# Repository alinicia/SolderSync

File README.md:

# SolderSync PCB Design
Modification of the T-962 reflow owen, ESP32 core with TFT LCD &amp; Custom Profiles

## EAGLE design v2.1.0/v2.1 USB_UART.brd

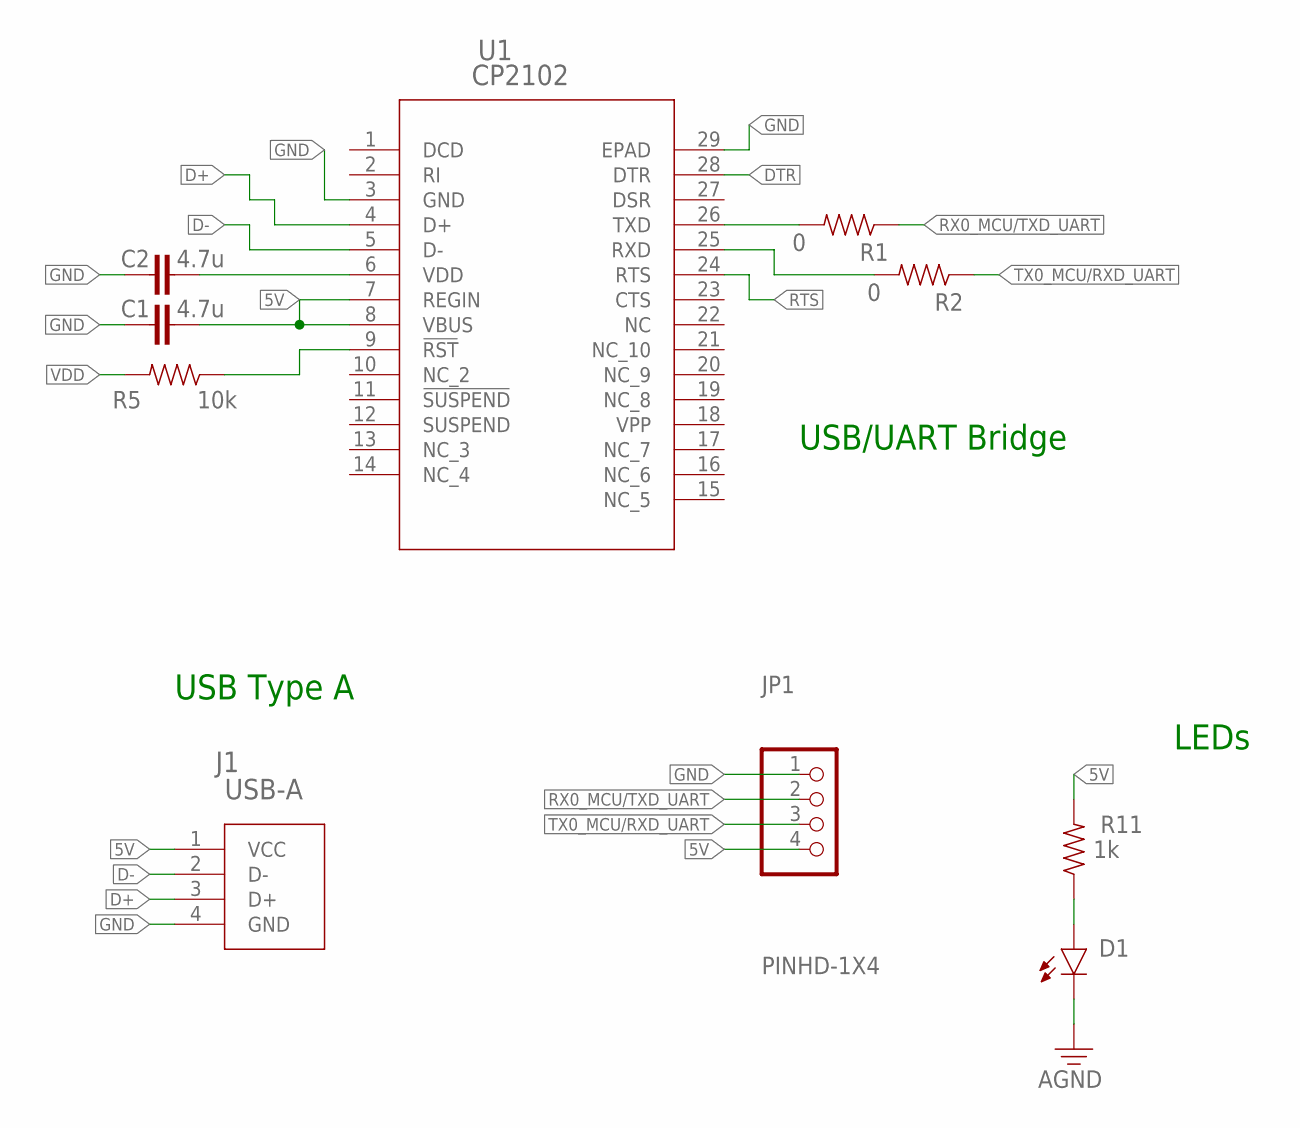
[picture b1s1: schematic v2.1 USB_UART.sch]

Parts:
C1, C2: 4.7u; CAPC2012X110
D1: LED; LEDC2012X110N_FLAT-B
J1: USB-A
JP1: PINHD-1X4; 1X04
R1, R2: 0; RESC2012X65
R5: 10k; RESC2012X65
R11: 1k; RESC2012X65
U1: CP2102; QFN28_5X5_SIL

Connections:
5V: C1.2, J1.1 (VCC), JP1.4, R11.2, U1.7 (REGIN), U1.8 (VBUS)
D+: J1.3 (D+), U1.4 (D+)
D-: J1.2 (D-), U1.5 (D-)
DTR: U1.28 (DTR)
GND: C1.1, C2.1, D1.C, J1.4 (GND), JP1.1, U1.3 (GND), U1.29 (EPAD)
unnamed: D1.A, R11.1
unnamed: R5.1, U1.9 (!RST)
RTS: U1.24 (RTS)
RX0_MCU/TXD_UART: JP1.2, R1.1
RXD: R2.2, U1.25 (RXD)
TX0_MCU/RXD_UART: JP1.3, R2.1
TXD: R1.2, U1.26 (TXD)
VDD: C2.2, R5.2, U1.6 (VDD)

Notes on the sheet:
USB/UART Bridge
USB Type A
LEDs

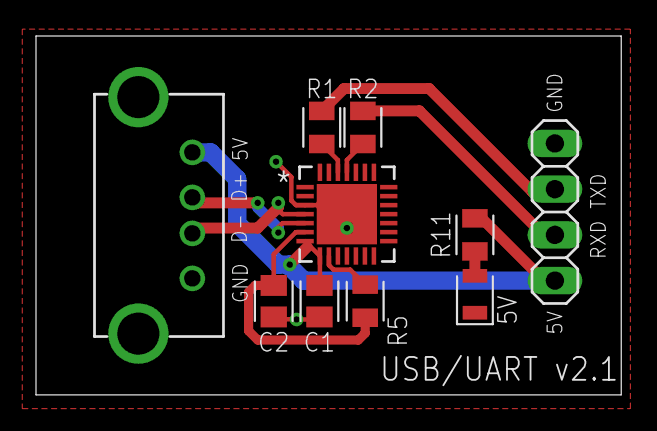
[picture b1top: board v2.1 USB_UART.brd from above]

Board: 2 copper layers, 32.5 x 19.9 mm, 10 parts (0 on the bottom side), 11 nets.

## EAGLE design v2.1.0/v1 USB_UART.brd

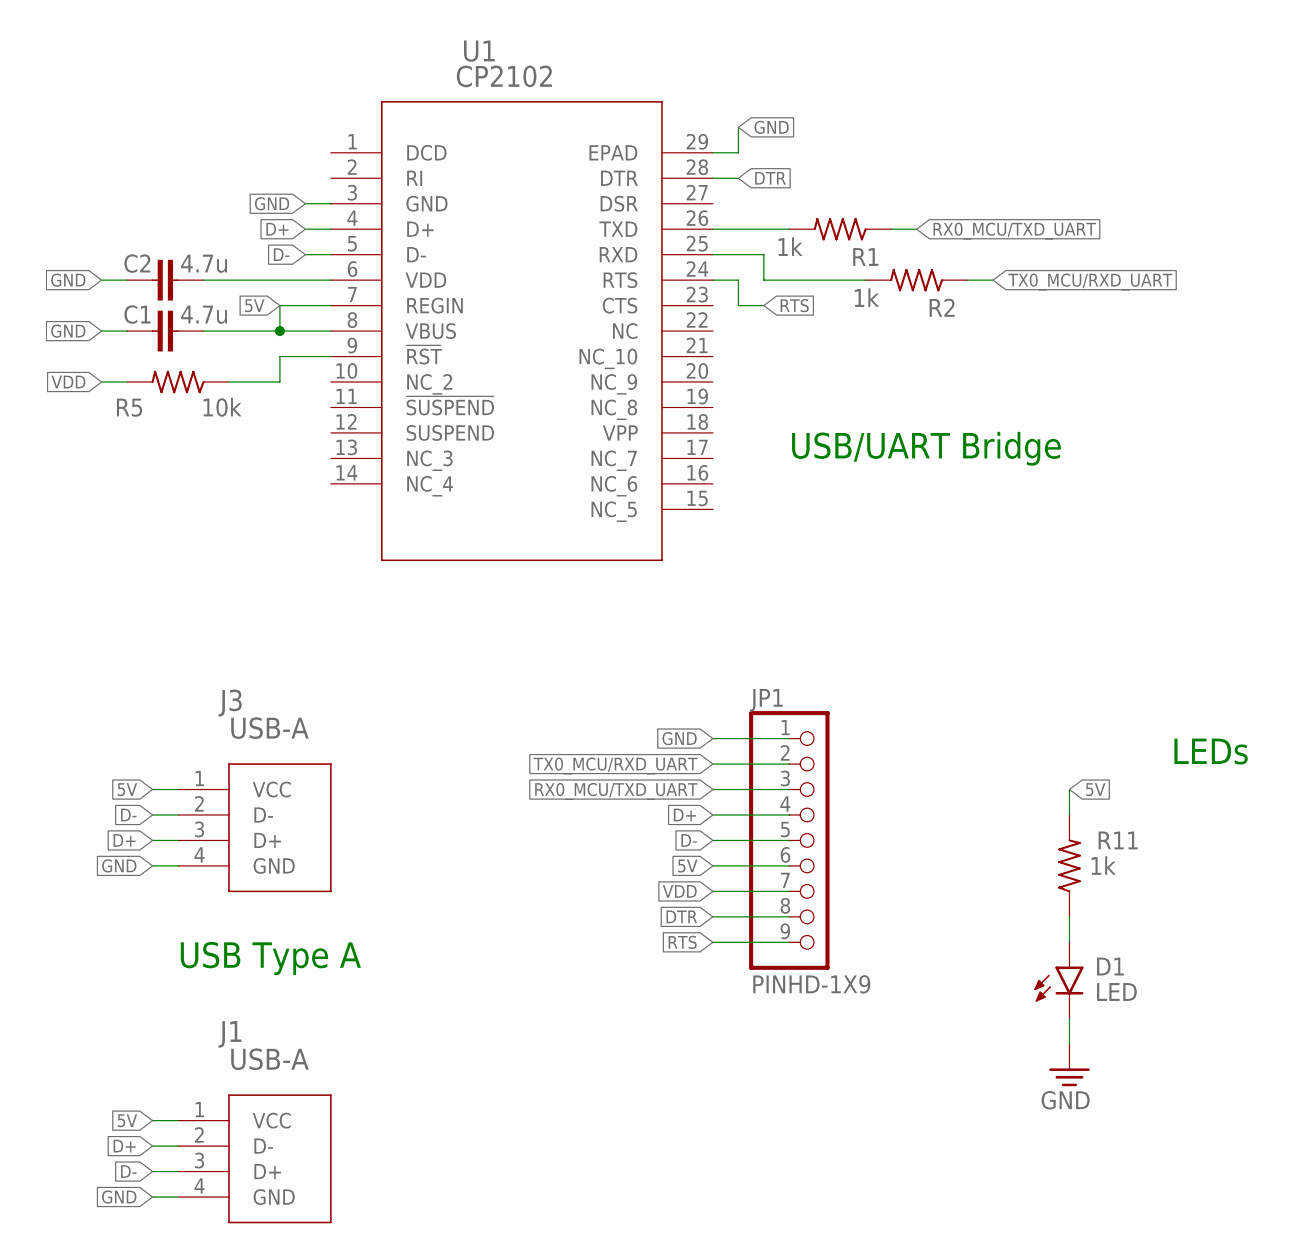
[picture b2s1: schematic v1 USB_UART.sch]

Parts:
C1, C2: 4.7u; CAPC2012X110
D1: LED; LEDC2012X110N_FLAT-B
J1, J3: USB-A
JP1: PINHD-1X9; 1X09
R1, R2, R11: 1k; RESC2012X65
R5: 10k; RESC2012X65
U1: CP2102; QFN28_5X5_SIL

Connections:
5V: C1.2, J1.1 (VCC), J3.1 (VCC), JP1.6, R11.2, U1.7 (REGIN), U1.8 (VBUS)
D+: J1.2 (D-), J3.3 (D+), JP1.4, U1.4 (D+)
D-: J1.3 (D+), J3.2 (D-), JP1.5, U1.5 (D-)
DTR: JP1.8, U1.28 (DTR)
GND: C1.1, C2.1, D1.C, J1.4 (GND), J3.4 (GND), JP1.1, U1.3 (GND), U1.29 (EPAD)
unnamed: D1.A, R11.1
unnamed: R5.1, U1.9 (!RST)
RTS: JP1.9, U1.24 (RTS)
RX0_MCU/TXD_UART: JP1.3, R1.1
RXD: R2.2, U1.25 (RXD)
TX0_MCU/RXD_UART: JP1.2, R2.1
TXD: R1.2, U1.26 (TXD)
VDD: C2.2, JP1.7, R5.2, U1.6 (VDD)

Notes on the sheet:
USB/UART Bridge
USB Type A
LEDs

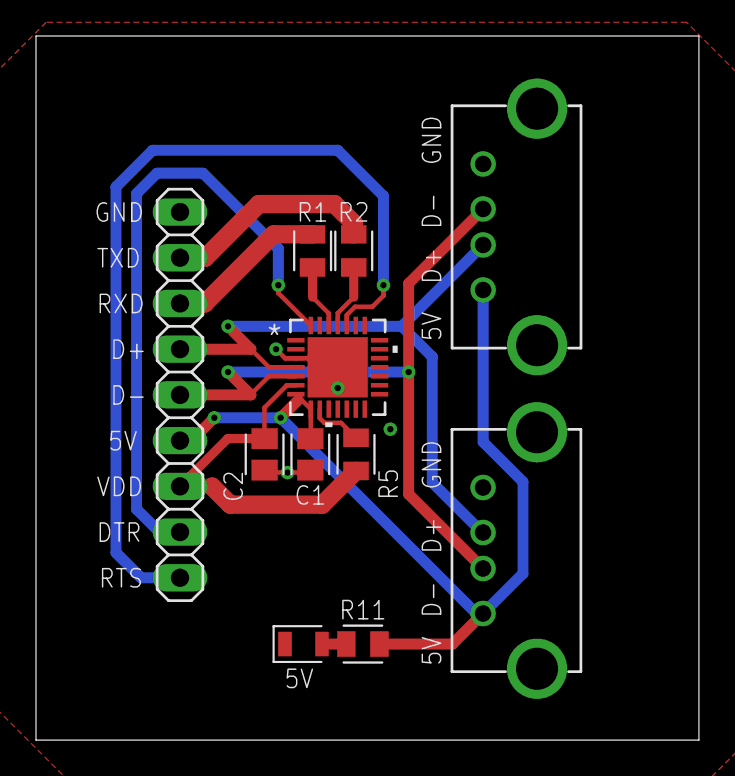
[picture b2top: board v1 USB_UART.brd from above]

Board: 2 copper layers, 36.8 x 39.1 mm, 11 parts (0 on the bottom side), 13 nets.

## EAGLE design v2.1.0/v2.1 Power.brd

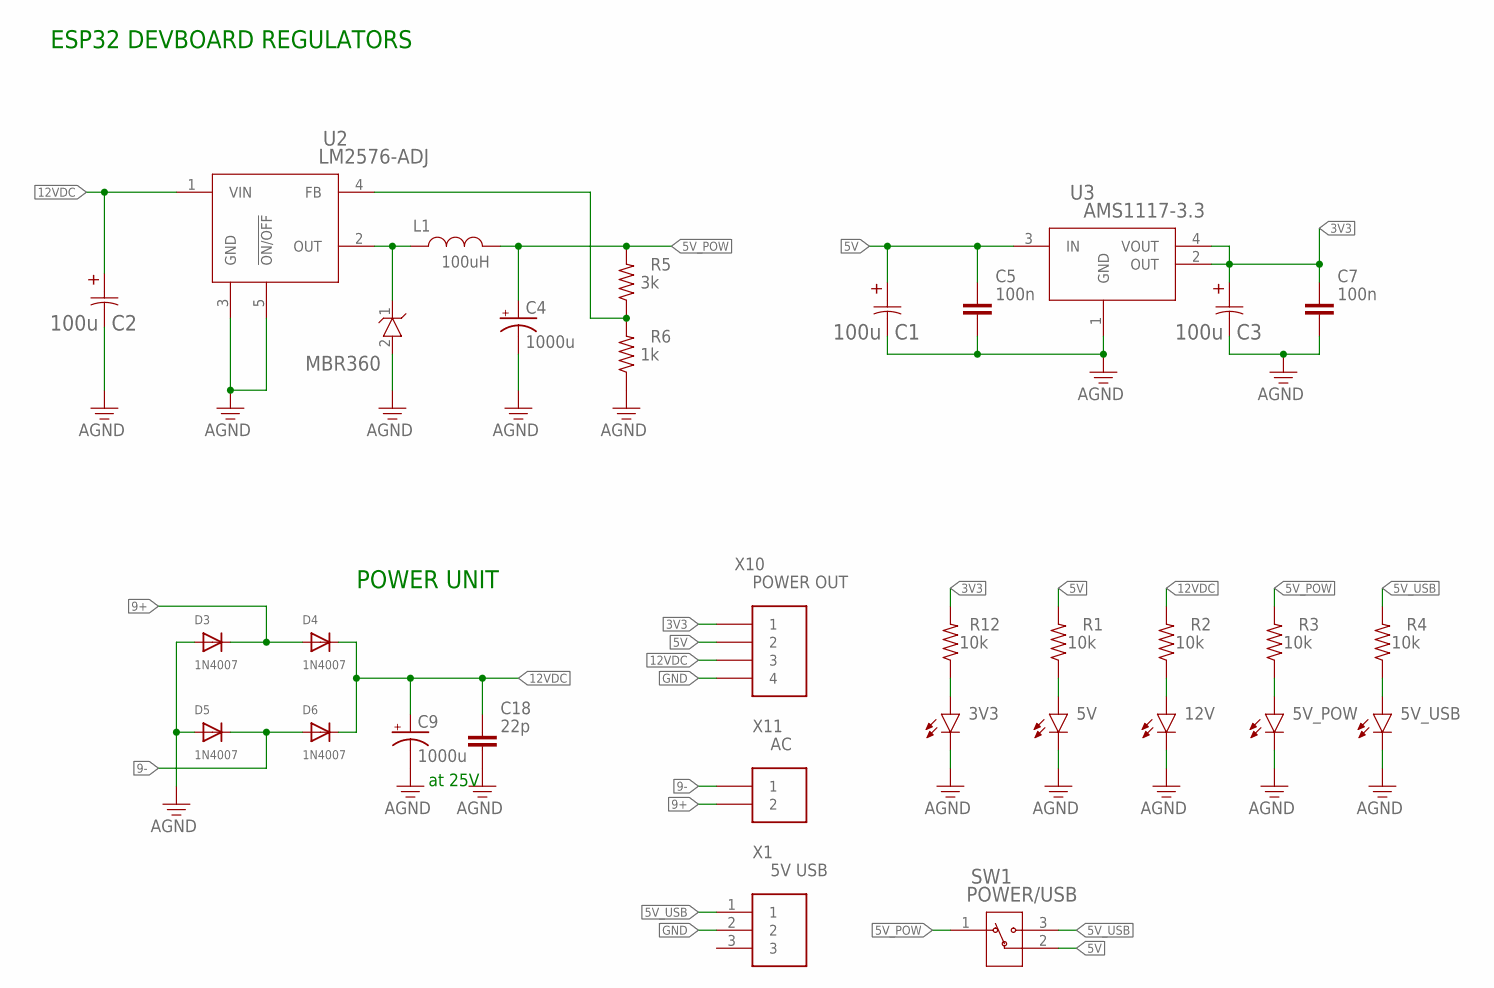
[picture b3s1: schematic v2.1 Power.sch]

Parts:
3V3, 5V, 5V_POW, 5V_USB, 12V: LED; LEDC2012X110N_FLAT-B
C1, C2, C3: 100u; 100UF_CAP
C4, C9: 1000u; CAP_10X20IN
C5, C7: 100n; CAPC2012X110
C18: 22p; CAPC2012X110
D3, D4, D5, D6: 1N4007; SOD-123FL
L1: 100uH; IND_MURATA_2200_MUR
MBR360: MBR360RLGDO-201AD_ONS; DO-201AD_ONS
R1, R2, R3, R4, R12: 10k; RESC2012X65
R5: 3k; RESC2012X65
R6: 1k; RESC2012X65
SW1: POWER/USB; SS-12D10G5_XKB
U2: LM2576-ADJ; T05A_TEX
U3: AMS1117-3.3; _ADS-L
X1: 5V USB; JST-XH-03-PACKAGE-LONG-PAD
X10: POWER OUT; JST-XH-04-PACKAGE-LONG-PAD
X11: AC; -LONG-PAD

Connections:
3V3: C3.1, C7.1, R12.2, U3.2 (OUT), U3.4 (VOUT), X10.1
5V: C1.1, C5.1, R1.2, SW1.2, U3.3 (IN), X10.2
5V_POW: C4.1 (+), L1.1, R3.2, R5.2, SW1.1
5V_USB: R4.2, SW1.3, X1.1
9+: D3.C, D4.A, X11.2
9-: D5.C, D6.A, X11.1
12VDC: C2.1, C9.1 (+), C18.1, D4.C, D6.C, R2.2, U2.1 (VIN), X10.3
FB: R5.1, R6.2, U2.4 (FB)
GND: 3V3.C, 5V.C, 5V_POW.C, 5V_USB.C, 12V.C, C1.2, C2.2, C3.2, C4.2 (-), C5.2, C7.2, C9.2 (-), C18.2, D3.A, D5.A, MBR360.2 (ANODE), R6.1, U2.3 (GND), U2.5 (!ON/OFF), U3.1 (GND), X1.2, X10.4
unnamed: 5V.A, R1.1
unnamed: L1.2, MBR360.1 (CATHODE), U2.2 (OUT)
unnamed: 12V.A, R2.1
unnamed: 5V_POW.A, R3.1
unnamed: 5V_USB.A, R4.1
unnamed: 3V3.A, R12.1

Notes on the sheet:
ESP32 DEVBOARD REGULATORS
POWER UNIT
at 25V

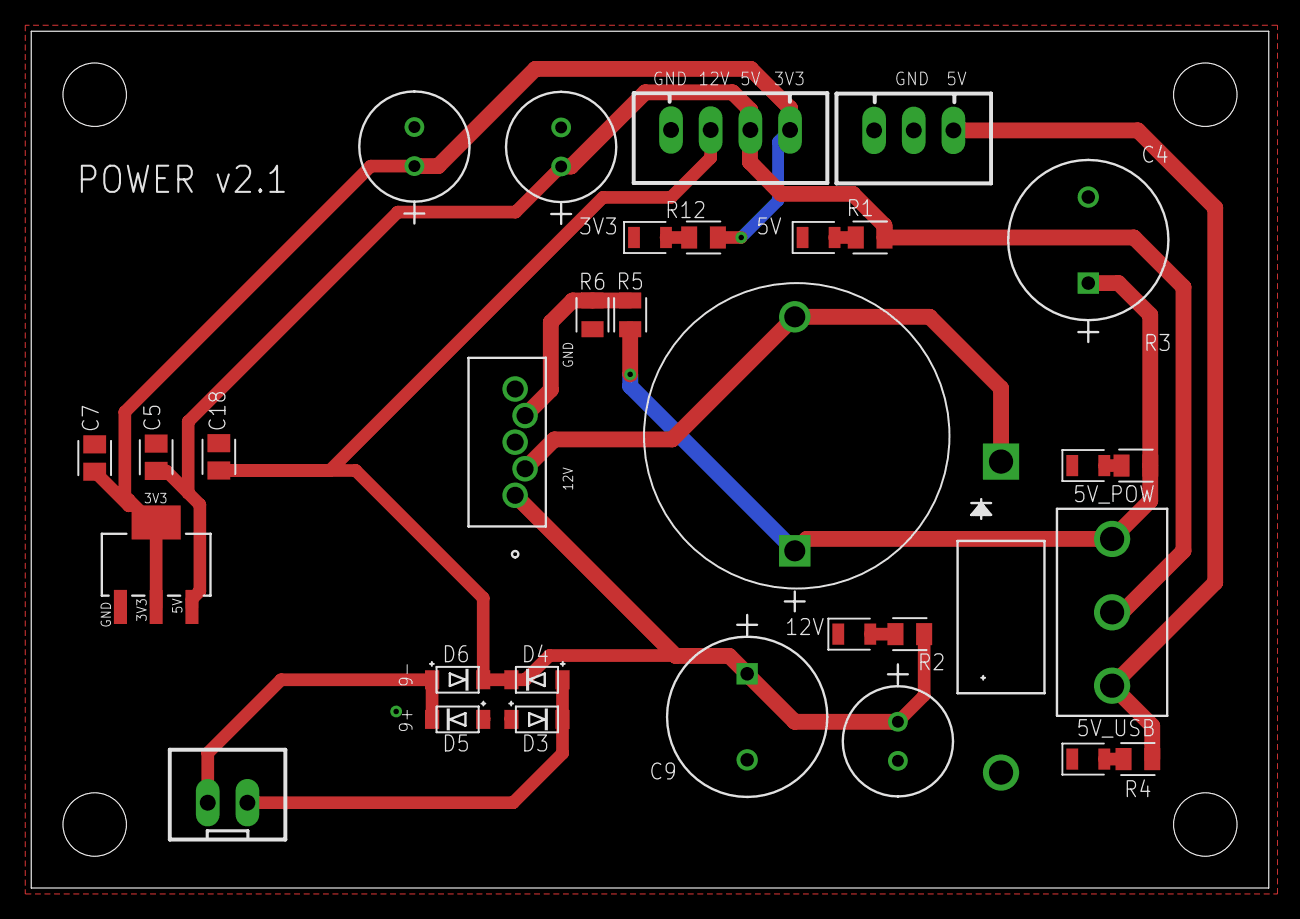
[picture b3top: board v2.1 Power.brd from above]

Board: 2 copper layers, 79.2 x 54.9 mm, 32 parts (0 on the bottom side), 15 nets.

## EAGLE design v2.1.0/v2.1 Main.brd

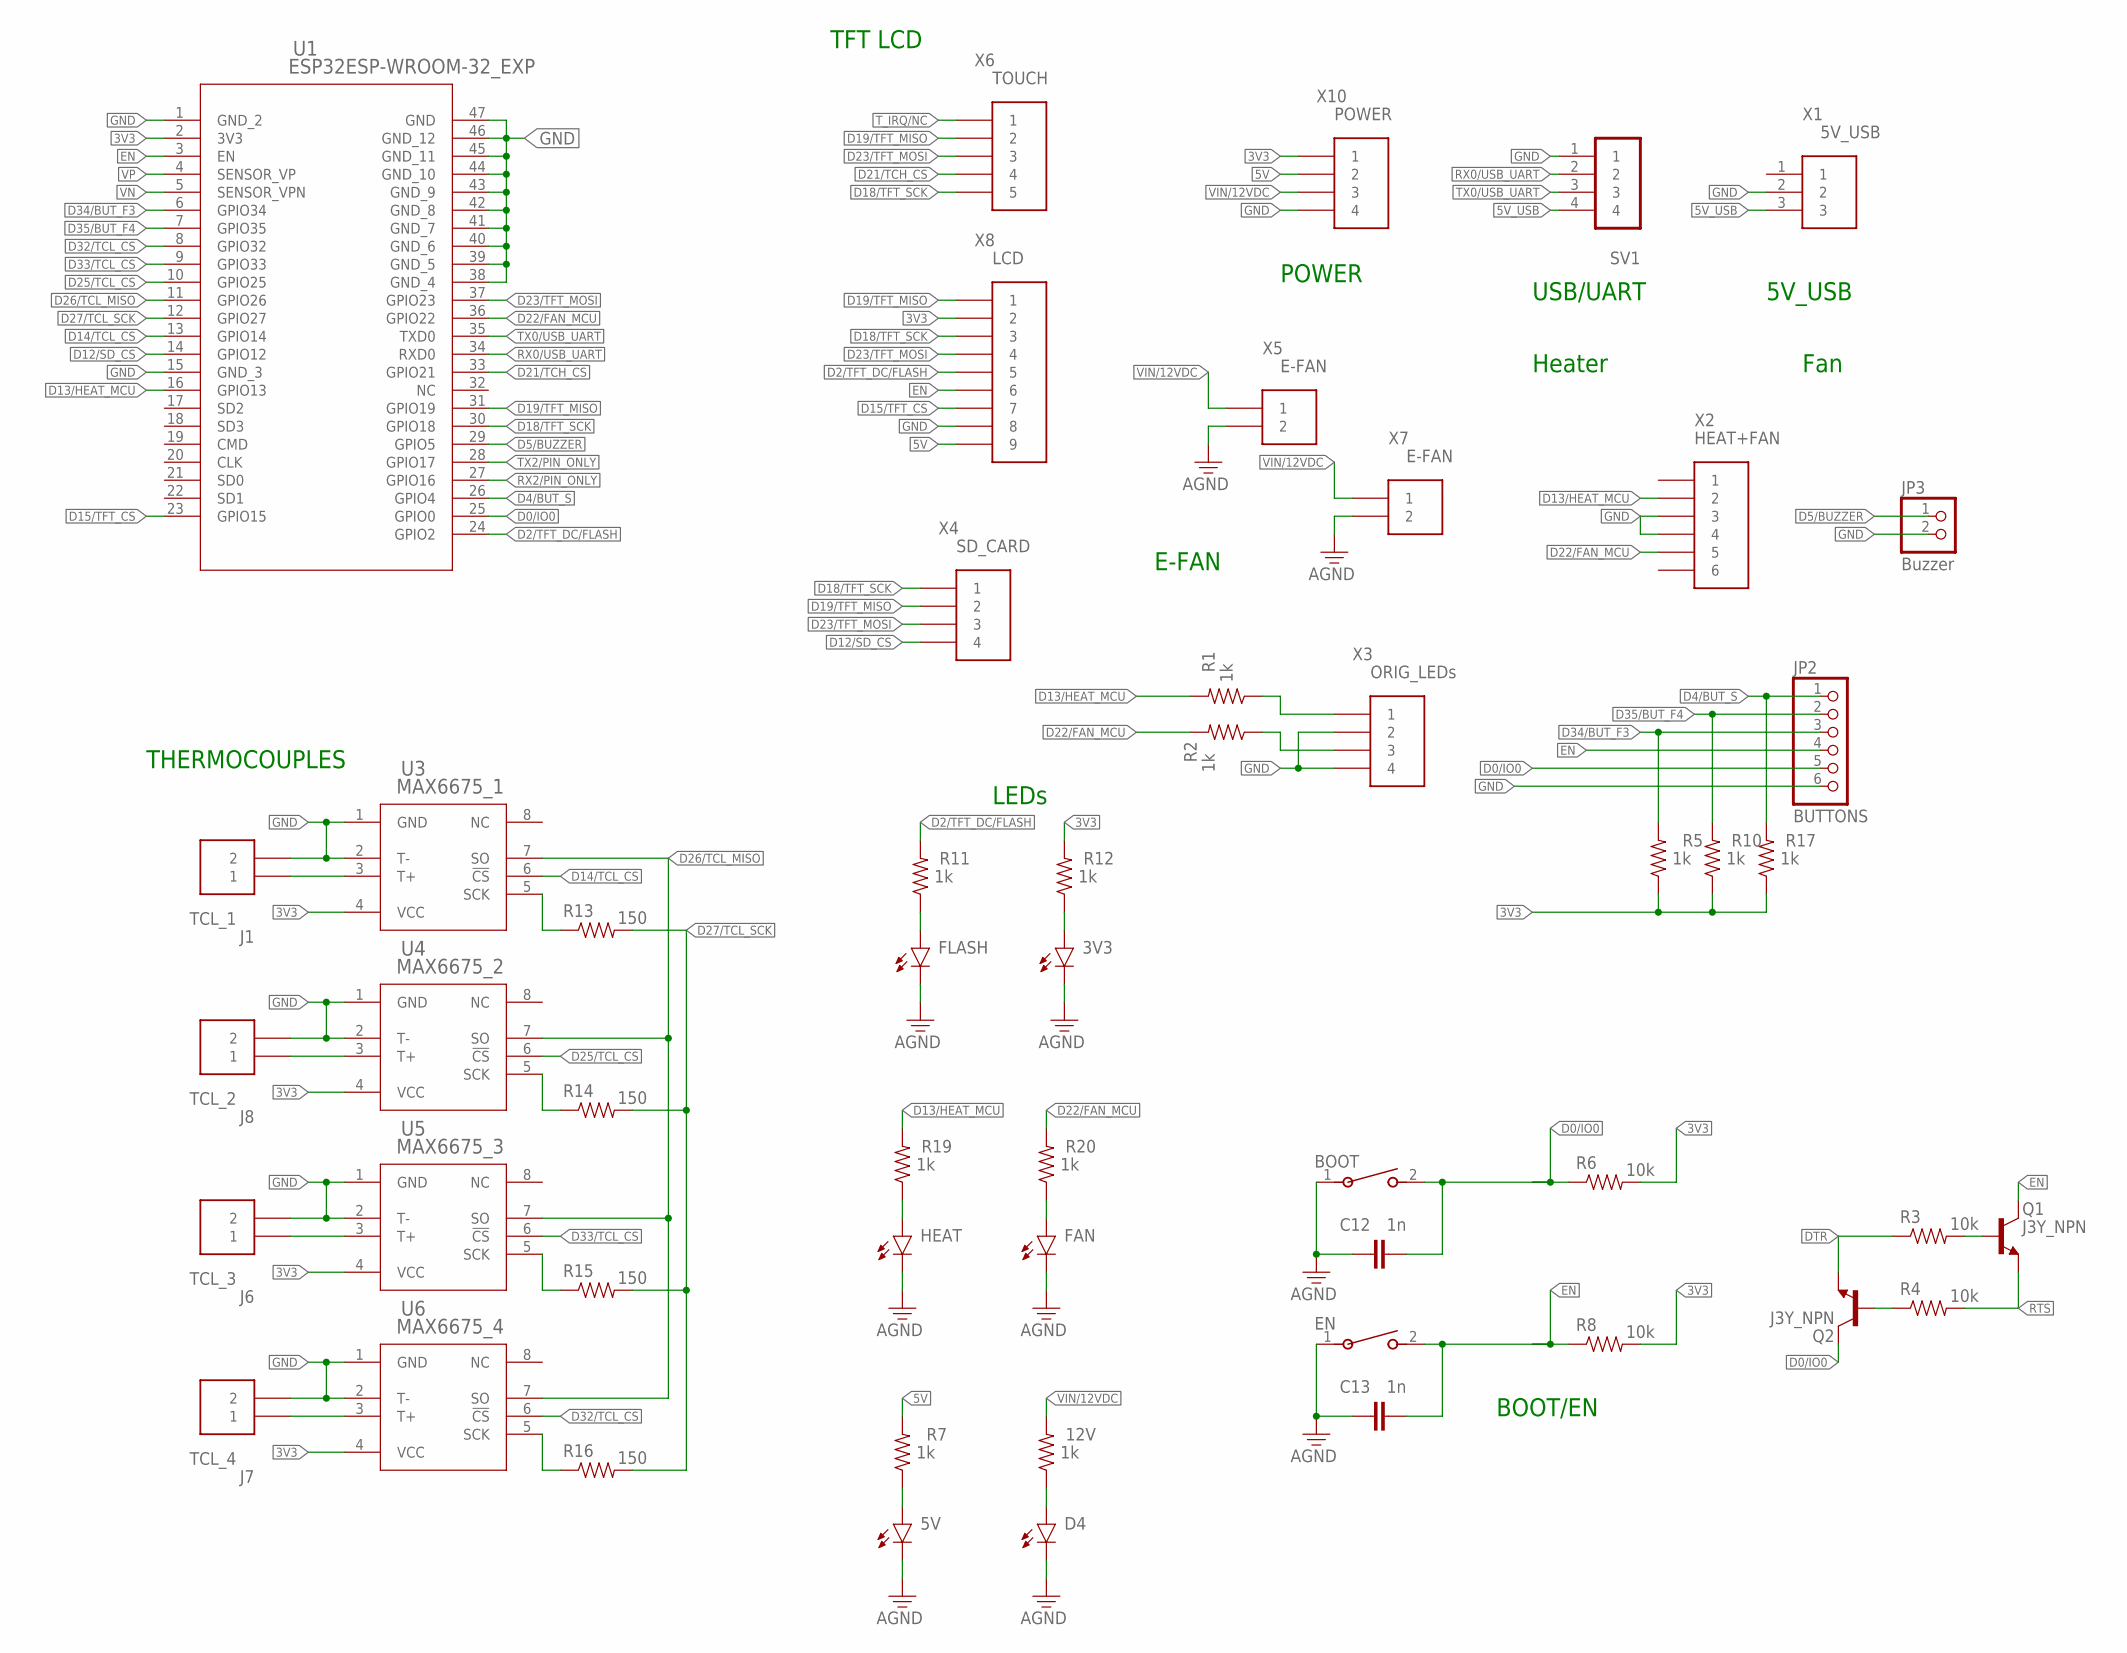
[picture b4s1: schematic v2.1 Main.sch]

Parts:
3V3, 5V: LED; LEDC2012X110N_FLAT-B
12V: 1k; RESC2012X65
BOOT: EVQ22705RSW_EVQ22705R_PAN; SW_EVQ22705R_PAN
C12, C13: 1n; CAPC2012X110
D4: LED; LEDC2012X110N_FLAT-B
EN: EVQ22705RSW_EVQ22705R_PAN; SW_EVQ22705R_PAN
FAN: LED; LEDC2012X110N_FLAT-B
FLASH: LED; LEDC2012X110N_FLAT-B
HEAT: LED; LEDC2012X110N_FLAT-B
J1: TCL_1; CONN_OSTVN02A150_OST
J6: TCL_3; CONN_OSTVN02A150_OST
J7: TCL_4; CONN_OSTVN02A150_OST
J8: TCL_2; CONN_OSTVN02A150_OST
JP2: BUTTONS; 1X06
JP3: Buzzer; 1X02
Q1, Q2: J3Y_NPN; SC59
R1, R2, R5, R7, R10, R11, R12, R17, R19, R20: 1k; RESC2012X65
R3, R4, R6, R8: 10k; RESC2012X65
R13, R14, R15, R16: 150; RESC2012X65
SV1: FEM-HEAD; FE05-1
U1: ESP32ESP-WROOM-32_EXP; ESP32_SCH_PCB
U3: MAX6675_1; 21-0041B_8_MXM
U4: MAX6675_2; 21-0041B_8_MXM
U5: MAX6675_3; 21-0041B_8_MXM
U6: MAX6675_4; 21-0041B_8_MXM
X1: 5V_USB; JST-XH-03-PACKAGE-LONG-PAD
X2: HEAT+FAN; JST-XH-06-PACKAGE-LONG-PAD
X3: ORIG_LEDs; JST-XH-04-PACKAGE-LONG-PAD
X4: SD_CARD; JST-XH-04-PACKAGE-LONG-PAD
X5, X7: E-FAN; -LONG-PAD
X6: TOUCH; JST-XH-05-PACKAGE-LONG-PAD
X8: LCD; JST-XH-09-PACKAGE-LONG-PAD
X10: POWER; JST-XH-04-PACKAGE-LONG-PAD

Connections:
3V3: R5.1, R6.2, R8.2, R10.1, R12.2, R17.1, U1.2 (3V3), U3.4 (VCC), U4.4 (VCC), U5.4 (VCC), U6.4 (VCC), X8.2, X10.1
5V: R7.2, X8.9, X10.2
5V_USB: SV1.4, X1.3
D0/IO0: BOOT.2, C12.2, JP2.5, Q2.C, R6.1, U1.25 (GPIO0)
D2/TFT_DC/FLASH: R11.2, U1.24 (GPIO2), X8.5
D4/BUT_S: JP2.1, R17.2, U1.26 (GPIO4)
D5/BUZZER: JP3.1, U1.29 (GPIO5)
D12/SD_CS: U1.14 (GPIO12), X4.4
D13/HEAT_MCU: R1.2, R19.2, U1.16 (GPIO13), X2.2
D14/TCL_CS: U1.13 (GPIO14), U3.6 (!CS)
D15/TFT_CS: U1.23 (GPIO15), X8.7
D18/TFT_SCK: U1.30 (GPIO18), X4.1, X6.5, X8.3
D19/TFT_MISO: U1.31 (GPIO19), X4.2, X6.2, X8.1
D21/TCH_CS: U1.33 (GPIO21), X6.4
D22/FAN_MCU: R2.2, R20.2, U1.36 (GPIO22), X2.5
D23/TFT_MOSI: U1.37 (GPIO23), X4.3, X6.3, X8.4
D25/TCL_CS: U1.10 (GPIO25), U4.6 (!CS)
D26/TCL_MISO: U1.11 (GPIO26), U3.7 (SO), U4.7 (SO), U5.7 (SO), U6.7 (SO)
D27/TCL_SCK: R13.2, R14.2, R15.2, R16.2, U1.12 (GPIO27)
D32/TCL_CS: U1.8 (GPIO32), U6.6 (!CS)
D33/TCL_CS: U1.9 (GPIO33), U5.6 (!CS)
D34/BUT_F3: JP2.3, R5.2, U1.6 (GPIO34)
D35/BUT_F4: JP2.2, R10.2, U1.7 (GPIO35)
DTR: Q2.E, R3.1
EN: C13.2, EN.2, JP2.4, Q1.C, R8.1, U1.3 (EN), X8.6
FAN_LED: R2.1, X3.3
GND: 3V3.C, 5V.C, BOOT.1, C12.1, C13.1, D4.C, EN.1, FAN.C, FLASH.C, HEAT.C, J1.2, J6.2, J7.2, J8.2, JP2.6, JP3.2, SV1.1, U1.1 (GND_2), U1.15 (GND_3), U1.38 (GND_4), U1.39 (GND_5), U1.40 (GND_6), U1.41 (GND_7), U1.42 (GND_8), U1.43 (GND_9), U1.44 (GND_10), U1.45 (GND_11), U1.46 (GND_12), U1.47 (GND), U3.1 (GND), U3.2 (T-), U4.1 (GND), U4.2 (T-), U5.1 (GND), U5.2 (T-), U6.1 (GND), U6.2 (T-), X1.2, X2.3, X2.4, X3.2, X3.4, X5.2, X7.2, X8.8, X10.4
HEAT_LED: R1.1, X3.1
unnamed: FLASH.A, R11.1
unnamed: Q1.B, R3.2
unnamed: Q2.B, R4.1
unnamed: 3V3.A, R12.1
unnamed: 5V.A, R7.1
unnamed: 12V.1, D4.A
unnamed: HEAT.A, R19.1
unnamed: FAN.A, R20.1
RTS: Q1.E, R4.2
RX0/USB_UART: SV1.2, U1.34 (RXD0)
RX2/PIN_ONLY: U1.27 (GPIO16)
T1: J1.1, U3.3 (T+)
T2: J8.1, U4.3 (T+)
T3: J6.1, U5.3 (T+)
T4: J7.1, U6.3 (T+)
TCL_SCK1: R13.1, U3.5 (SCK)
TCL_SCK2: R14.1, U4.5 (SCK)
TCL_SCK3: R15.1, U5.5 (SCK)
TCL_SCK4: R16.1, U6.5 (SCK)
TX0/USB_UART: SV1.3, U1.35 (TXD0)
TX2/PIN_ONLY: U1.28 (GPIO17)
T_IRQ/NC: X6.1
VIN/12VDC: 12V.2, X5.1, X7.1, X10.3
VN: U1.5 (SENSOR_VPN)
VP: U1.4 (SENSOR_VP)

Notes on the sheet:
TFT LCD
BOOT/EN
LEDs
THERMOCOUPLES
E-FAN
POWER
Heater
Fan
USB/UART
5V_USB

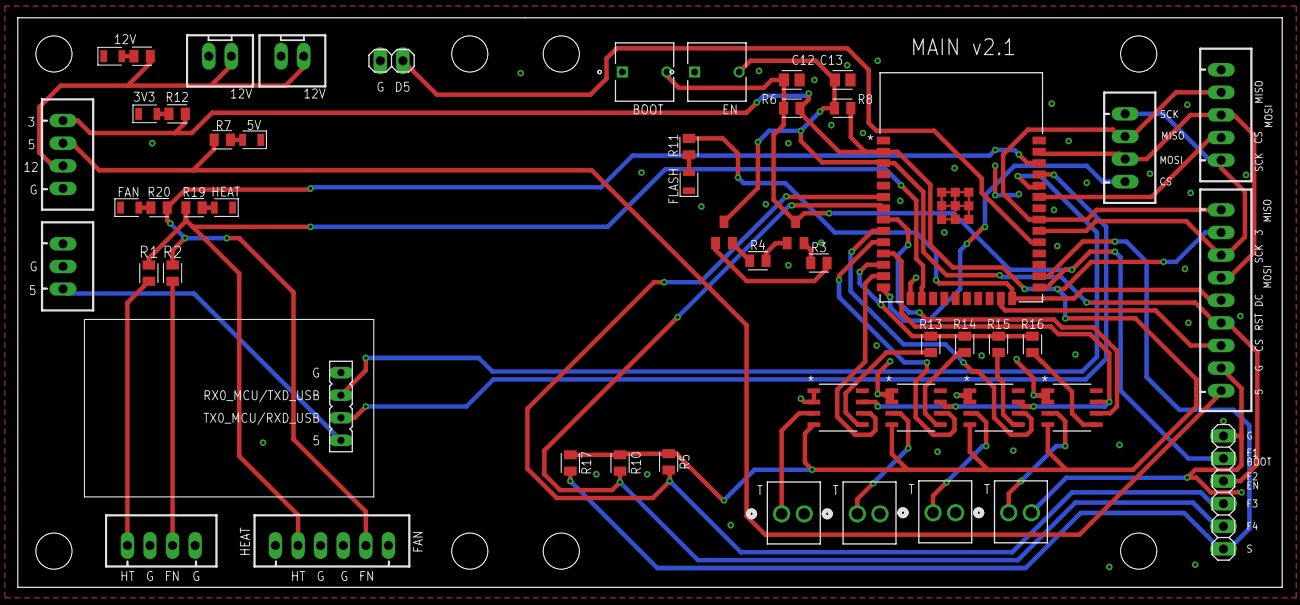
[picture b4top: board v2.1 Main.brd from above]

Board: 2 copper layers, 142.1 x 64.0 mm, 52 parts (0 on the bottom side), 48 nets.

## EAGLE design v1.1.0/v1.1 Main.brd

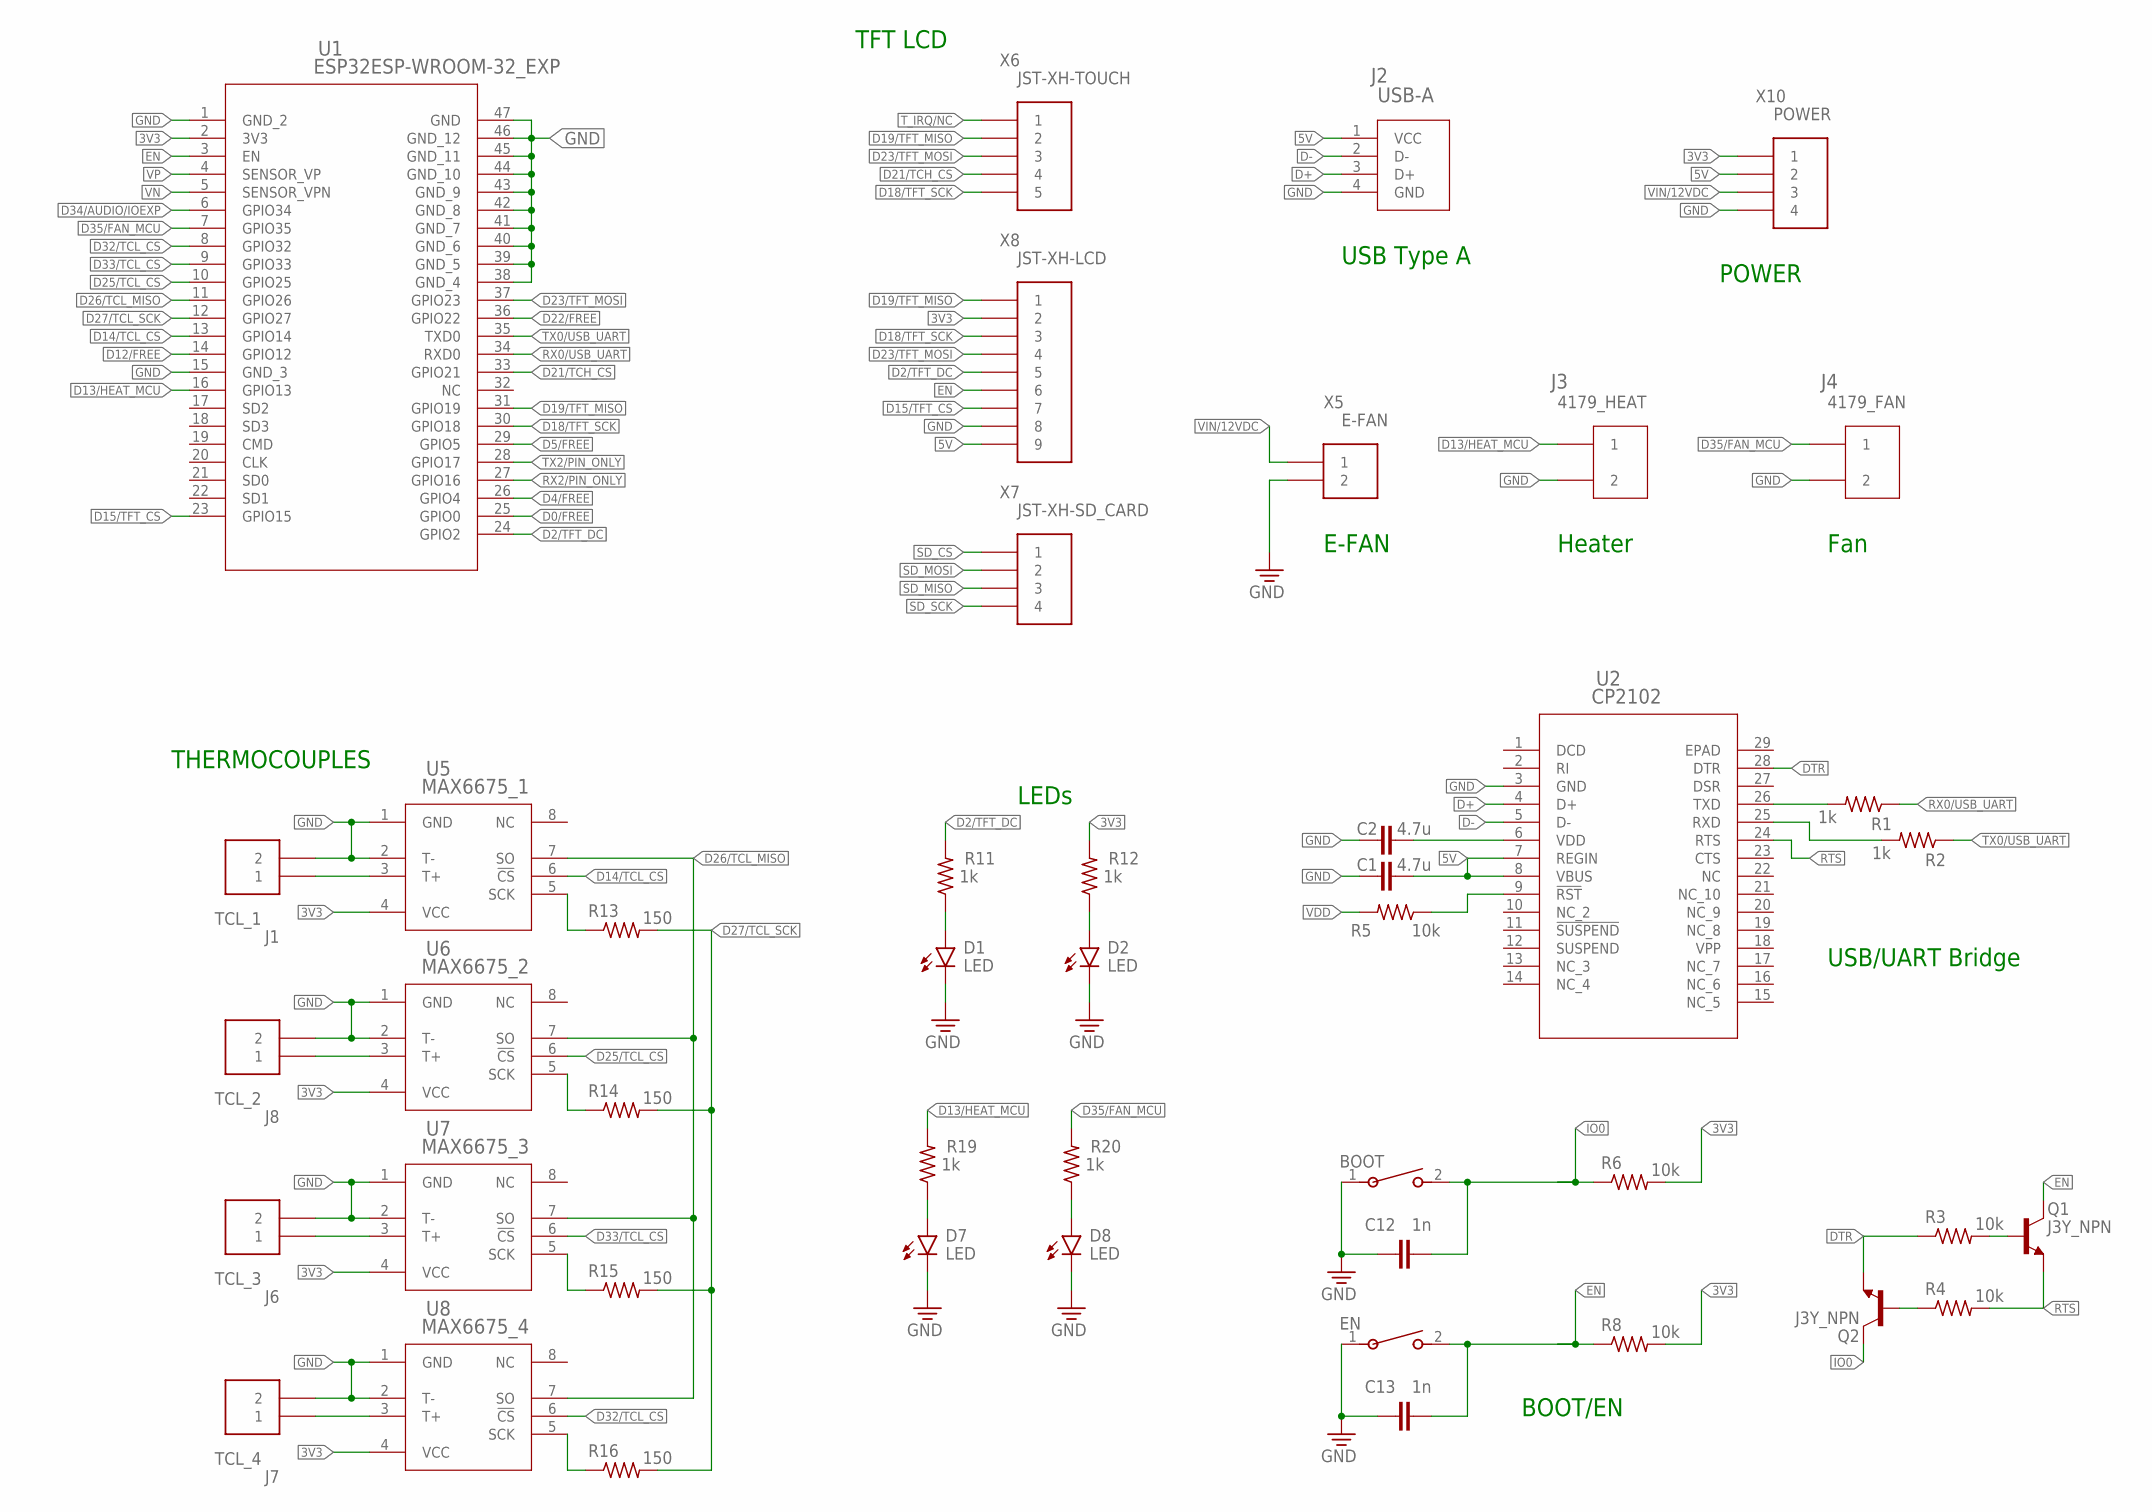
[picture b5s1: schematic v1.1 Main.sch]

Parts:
BOOT: EVQ22705RSW_EVQ22705R_PAN; SW_EVQ22705R_PAN
C1, C2: 4.7u; CAPC2012X110
C12, C13: 1n; CAPC2012X110
D1, D2, D7, D8: LED; LEDC2012X110N_FLAT-B
EN: EVQ22705RSW_EVQ22705R_PAN; SW_EVQ22705R_PAN
J1: TCL_1; CONN_OSTVN02A150_OST
J2: USB-A
J3: 4179_HEAT; 41791
J4: 4179_FAN; 41791
J6: TCL_3; CONN_OSTVN02A150_OST
J7: TCL_4; CONN_OSTVN02A150_OST
J8: TCL_2; CONN_OSTVN02A150_OST
Q1, Q2: J3Y_NPN; SC59
R1, R2, R11, R12, R19, R20: 1k; RESC2012X65
R3, R4, R5, R6, R8: 10k; RESC2012X65
R13, R14, R15, R16: 150; RESC2012X65
U1: ESP32ESP-WROOM-32_EXP; ESP32_SCH_PCB
U2: CP2102; QFN28_5X5_SIL
U5: MAX6675_1; _ISA_MXM
U6: MAX6675_2; _ISA_MXM
U7: MAX6675_3; _ISA_MXM
U8: MAX6675_4; _ISA_MXM
X5: E-FAN; -LONG-PAD
X6: JST-XH-TOUCH; JST-XH-05-PACKAGE-LONG-PAD
X7: JST-XH-SD_CARD; JST-XH-04-PACKAGE-LONG-PAD
X8: JST-XH-LCD; JST-XH-09-PACKAGE-LONG-PAD
X10: POWER; JST-XH-04-PACKAGE-LONG-PAD

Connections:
3V3: R6.2, R8.2, R12.2, U1.2 (3V3), U5.4 (VCC), U6.4 (VCC), U7.4 (VCC), U8.4 (VCC), X8.2, X10.1
5V: C1.2, J2.1 (VCC), U2.7 (REGIN), U2.8 (VBUS), X8.9, X10.2
D0/FREE: U1.25 (GPIO0)
D2/TFT_DC: R11.2, U1.24 (GPIO2), X8.5
D4/FREE: U1.26 (GPIO4)
D5/FREE: U1.29 (GPIO5)
D12/FREE: U1.14 (GPIO12)
D13/HEAT_MCU: J3.1, R19.2, U1.16 (GPIO13)
D14/TCL_CS: U1.13 (GPIO14), U5.6 (!CS)
D15/TFT_CS: U1.23 (GPIO15), X8.7
D18/TFT_SCK: U1.30 (GPIO18), X6.5, X8.3
D19/TFT_MISO: U1.31 (GPIO19), X6.2, X8.1
D21/TCH_CS: U1.33 (GPIO21), X6.4
D22/FREE: U1.36 (GPIO22)
D23/TFT_MOSI: U1.37 (GPIO23), X6.3, X8.4
D25/TCL_CS: U1.10 (GPIO25), U6.6 (!CS)
D26/TCL_MISO: U1.11 (GPIO26), U5.7 (SO), U6.7 (SO), U7.7 (SO), U8.7 (SO)
D27/TCL_SCK: R13.2, R14.2, R15.2, R16.2, U1.12 (GPIO27)
D32/TCL_CS: U1.8 (GPIO32), U8.6 (!CS)
D33/TCL_CS: U1.9 (GPIO33), U7.6 (!CS)
D34/AUDIO/IOEXP: U1.6 (GPIO34)
D35/FAN_MCU: J4.1, R20.2, U1.7 (GPIO35)
D+: J2.3 (D+), U2.4 (D+)
D-: J2.2 (D-), U2.5 (D-)
DTR: Q2.E, R3.1, U2.28 (DTR)
EN: C13.2, EN.2, Q1.C, R8.1, U1.3 (EN), X8.6
GND: BOOT.1, C1.1, C2.1, C12.1, C13.1, D1.C, D2.C, D7.C, D8.C, EN.1, J1.2, J2.4 (GND), J3.2, J4.2, J6.2, J7.2, J8.2, U1.1 (GND_2), U1.15 (GND_3), U1.38 (GND_4), U1.39 (GND_5), U1.40 (GND_6), U1.41 (GND_7), U1.42 (GND_8), U1.43 (GND_9), U1.44 (GND_10), U1.45 (GND_11), U1.46 (GND_12), U1.47 (GND), U2.3 (GND), U5.1 (GND), U5.2 (T-), U6.1 (GND), U6.2 (T-), U7.1 (GND), U7.2 (T-), U8.1 (GND), U8.2 (T-), X5.2, X8.8, X10.4
IO0: BOOT.2, C12.2, Q2.C, R6.1
unnamed: D1.A, R11.1
unnamed: Q1.B, R3.2
unnamed: R1.2, U2.26 (TXD)
unnamed: Q2.B, R4.1
unnamed: R5.1, U2.9 (!RST)
unnamed: D2.A, R12.1
unnamed: D7.A, R19.1
unnamed: D8.A, R20.1
RTS: Q1.E, R4.2, U2.24 (RTS)
RX0/USB_UART: R1.1, U1.34 (RXD0)
RX2/PIN_ONLY: U1.27 (GPIO16)
RXD: R2.2, U2.25 (RXD)
SD_CS: X7.1
SD_MISO: X7.3
SD_MOSI: X7.2
SD_SCK: X7.4
T1: J1.1, U5.3 (T+)
T2: J8.1, U6.3 (T+)
T3: J6.1, U7.3 (T+)
T4: J7.1, U8.3 (T+)
TCL_SCK1: R13.1, U5.5 (SCK)
TCL_SCK2: R14.1, U6.5 (SCK)
TCL_SCK3: R15.1, U7.5 (SCK)
TCL_SCK4: R16.1, U8.5 (SCK)
TX0/USB_UART: R2.1, U1.35 (TXD0)
TX2/PIN_ONLY: U1.28 (GPIO17)
T_IRQ/NC: X6.1
VDD: C2.2, R5.2, U2.6 (VDD)
VIN/12VDC: X5.1, X10.3
VN: U1.5 (SENSOR_VPN)
VP: U1.4 (SENSOR_VP)

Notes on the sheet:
TFT LCD
USB Type A
USB/UART Bridge
BOOT/EN
LEDs
THERMOCOUPLES
E-FAN
POWER
Heater
Fan

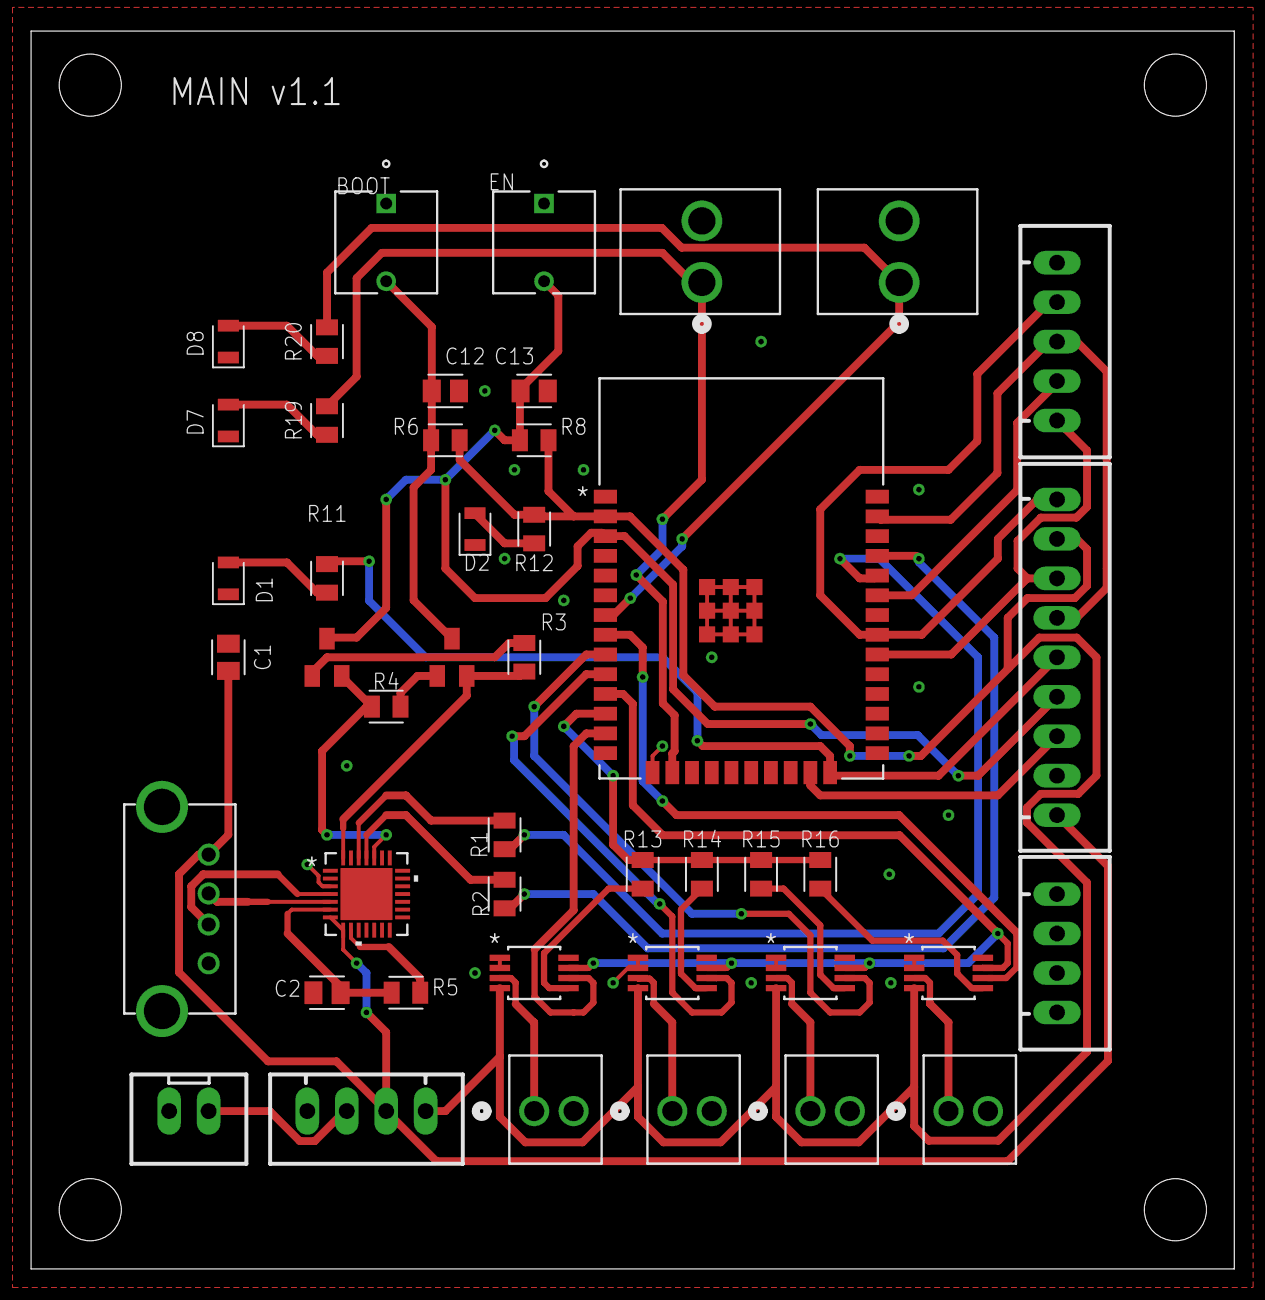
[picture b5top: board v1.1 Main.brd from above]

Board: 2 copper layers, 77.5 x 79.7 mm, 45 parts (0 on the bottom side), 44 nets.

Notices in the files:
parts and their libraries:
COPYRIGHT: Copyright (C) 2024 Ultra Librarian. All rights reserved.
COPYRIGHT: Copyright (C) 2025 Ultra Librarian. All rights reserved.
